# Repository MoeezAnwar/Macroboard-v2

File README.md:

# 🧠 Macroboard v2 — Compact 4-Key Mechanical Macro Pad with Rotary Encoder

**Macroboard v2** is a compact, hot-swappable **4-key mechanical macro pad** featuring a high-quality rotary encoder, designed by **Moeez Anwar**. It’s perfect for streamlining workflows, creative shortcuts, and gaming macros. This open-source project includes full PCB design, schematics, 3D models, and all necessary files to build your own Macroboard.

---

## 📦 Repository Structure

| Folder/File                     | Description                                                                 |
|--------------------------------|-----------------------------------------------------------------------------|
| `Macroboard-v2.kicad_sch`      | Electrical schematic designed in KiCad.                                     |
| `Macroboard-v2.kicad_pcb`      | PCB layout file.                                                            |
| `Macroboard-v2.step`           | 3D STEP model of the assembled macro pad with components.                   |
| `Macroboard-v2.csv`            | Bill of Materials (BOM) including part prices and sources.                  |
| `Gerber/`                      | Complete Gerber files ready for PCB fabrication.                            |
| `3d Model/`                    | STL and STEP files for 3D-printable case/enclosure.                         |
| `AutoDesk Project File/`       | Fusion 360 project files for case customization.                            |
| `images/`                      | Photos, renders, and other visual references.                               |
| `JOURNAL.md`                   | Development and design notes.                                               |
| `.gitignore`                   | Git ignore file.                                                            |
| `README.md`                    | This document.                                                              |

---

## 🧰 Features

- ✅ **4 Mechanical Keys** — Minimalist layout for essential macros.
- ✅ **Rotary Encoder** — Smooth, precise control for volume, scrolling, or custom functions.
- ✅ **Kailh Hot-Swap Sockets** — Easily swap switches without soldering.
- ✅ **MX-Style Switch Compatible** — Supports all Cherry MX-style switches.
- ✅ **USB-C Connector** — Modern, reversible connection interface.
- ✅ **QMK / VIA Firmware Compatible** — Full programmability and customization.
- ✅ **Open Source Hardware & Software** — Full transparency and freedom to customize.

---

## 🛠️ Bill of Materials (BOM)

The full BOM is detailed in [Macroboard-v2.csv](Macroboard-v2.csv), including:

- Kailh hot-swap sockets
- Recommended switches (e.g., Kailh Speed Pro Heavy / Super Speed)
- Rotary encoder (e.g., DCR_PEC12R-4015F-S0024)
- LEDs (SMD 1206 package)
- NPN transistors (SOT-23 package) for LED control
- SMD resistors (0603 package)
- Microcontroller and USB-C connector (not included in the repo)

Prices and supplier info included.

---

## 🖨️ 3D Printed Case

Included are 3D-printable case files located in the [`3d Model/`](./3d%20Model) and [`AutoDesk Project File/`](./AutoDesk%20Project%20File) folders. The case is designed to protect the PCB and provide a sleek, ergonomic enclosure.

---

## 📤 Manufacturing Instructions

1. Upload the Gerber files in the `Gerber/` folder to your PCB manufacturer of choice (e.g., JLCPCB, PCBWay).
2. Select 1.6mm FR4, 2-layer PCB, HASL finish.
3. Order and wait for delivery.
4. Assemble components following the schematic and BOM.

---

## 🧪 Getting Started

1. Clone the repository:
   ```bash
   git clone https://github.com/MoeezAnwar/Macroboard-v2.git
   cd Macroboard-v2
Open and edit the project in KiCad 7+.

Program the microcontroller with QMK or compatible firmware to customize key mappings and encoder behavior.

---

## ✍️ Author

**Moeez Anwar**  
Founder, Flurryhost  
[LinkedIn](https://linkedin.com/in/MoeezAnwar) 

---

## 🛡️ License

Open source under the [MIT License](LICENSE.txt). Feel free to use, modify, and share with credit.

---

## 🙏 Acknowledgments

Thanks to the KiCad community and open hardware advocates for enabling projects like this.

---

Share your builds and improvements! Contributions and issues are welcome.

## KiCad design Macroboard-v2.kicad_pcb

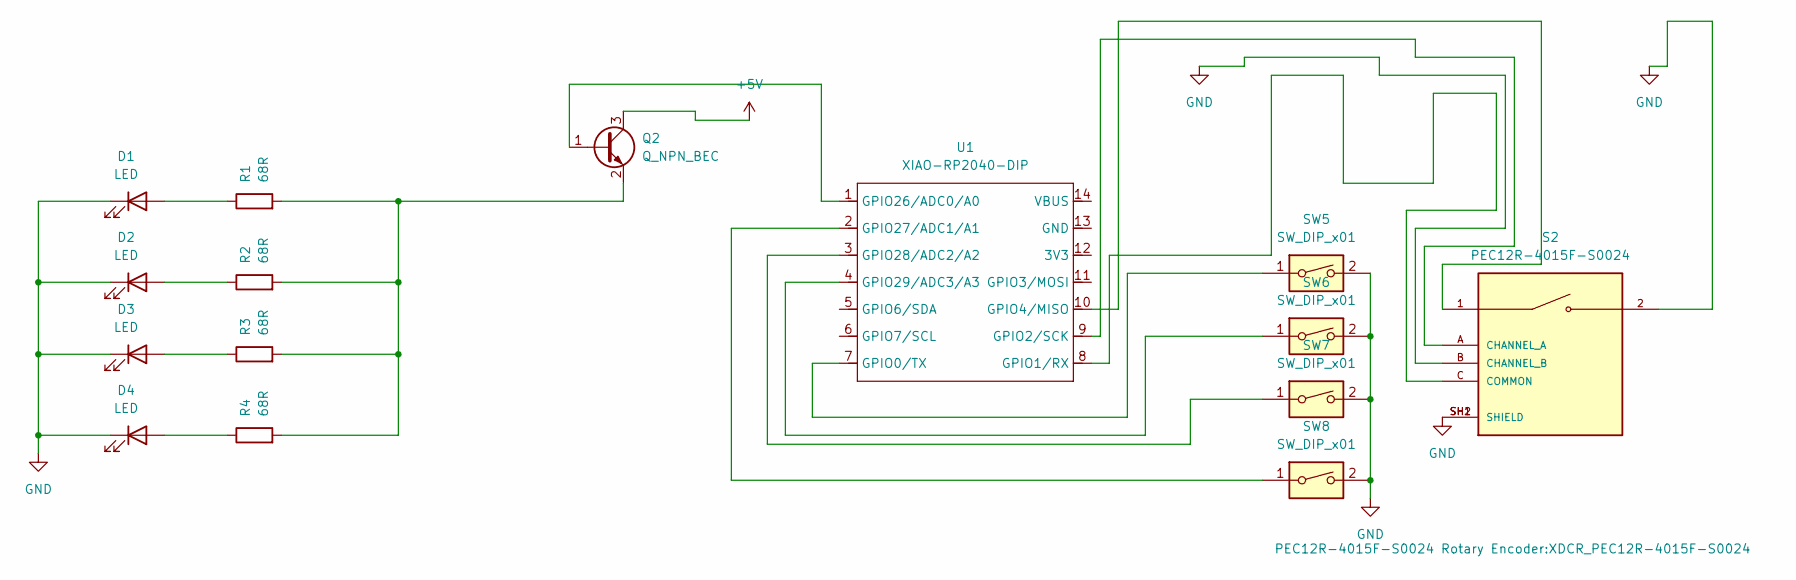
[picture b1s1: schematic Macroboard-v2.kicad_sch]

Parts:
D1, D2, D3, D4: LED; LED_1206_3216Metric
Q2: Q_NPN_BEC; SOT-23
R1, R2, R3, R4: 68R; R_0603_1608Metric
S2: PEC12R-4015F-S0024; XDCR_PEC12R-4015F-S0024; PARTREV 07/21
SW5, SW6, SW7, SW8: SW_DIP_x01; Kailh_socket_MX
U1: XIAO-RP2040-DIP

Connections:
+5V: Q2.3 (C)
GND: D1.1 (K), D2.1 (K), D3.1 (K), D4.1 (K), S2.2, S2.B (CHANNEL_B), S2.SH1 (SHIELD), S2.SH2 (SHIELD), SW5.2, SW6.2, SW7.2, SW8.2
unnamed: D1.2 (A), R1.1
unnamed: D2.2 (A), R2.1
unnamed: D3.2 (A), R3.1
unnamed: D4.2 (A), R4.1
unnamed: Q2.1 (B), U1.1 (GPIO26/ADC0/A0)
unnamed: Q2.2 (E), R1.2, R2.2, R3.2, R4.2
unnamed: S2.A (CHANNEL_A), U1.9 (GPIO2/SCK)
unnamed: S2.C (COMMON), U1.8 (GPIO1/RX)
unnamed: SW5.1, U1.7 (GPIO0/TX)
unnamed: S2.1, U1.10 (GPIO4/MISO)
unnamed: SW8.1, U1.2 (GPIO27/ADC1/A1)
unnamed: SW7.1, U1.3 (GPIO28/ADC2/A2)
unnamed: SW6.1, U1.4 (GPIO29/ADC3/A3)

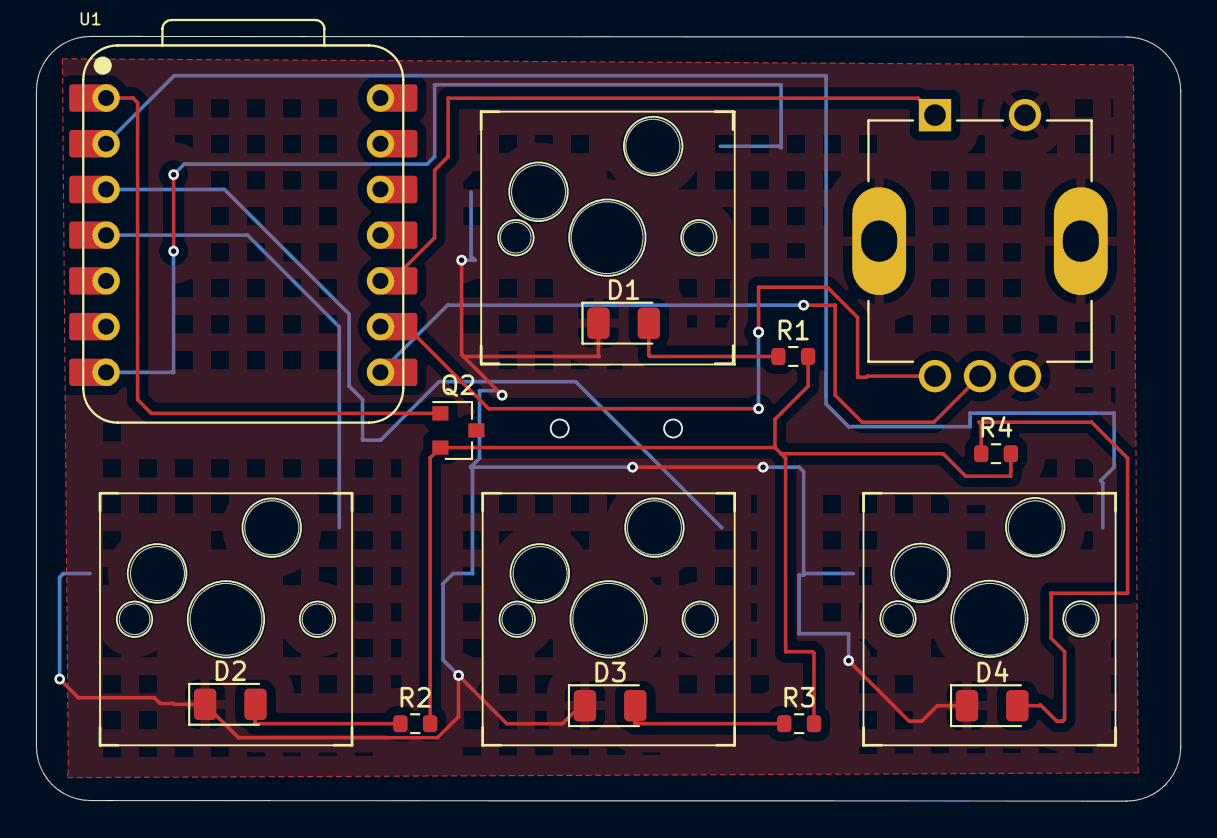
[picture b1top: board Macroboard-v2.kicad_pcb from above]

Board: 2 copper layers, 63.6 x 42.5 mm, 15 parts (0 on the bottom side), 14 nets.

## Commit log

2025-05-21 Initial commit: Add KiCad project files
2025-05-21 Create JOURNALmd
2025-05-21 Update JOURNALmd
2025-05-21 Images
2025-05-21 Image-20250521
2025-05-21 18:51 - 2025-5-21
2025-05-21 20:49 - 2025-5-21
2025-05-21 added .gitignore file
2025-05-21 Remove unwanted backup and temp files from repository
2025-05-21 Rename JOURNALmd to JOURNAL.md
2025-05-21 Picture of Schemetics &PCB
2025-05-22 Adding Rotary Encoder to the macroboard . Added led Light and added Hot swapable switches
2025-05-22 Schemetics and PCB Desing completed . T- 1756 -20250522
2025-05-22 Added 3d Model for the the footprint and made some minor changes
2025-05-22 Modified Files - Updated Journal.md
2025-05-23 Final Commit . All changes made . Created Case for macroboard , added 3d models
2025-05-23 Changes made to journal
2025-05-23 Added BOM + Prices for the parts and Added Gerber File
2025-05-23 Modified Readme file and added license file
2025-05-23 Change formetting of Macroboard-v2.csv
2025-05-31 Minor Changes
2025-06-02 Added Screw holes
